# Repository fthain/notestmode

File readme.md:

## notestmode - PCB and PLD designs

(c) Finn Thain 2024-2025

This project is a test rig for a logic circuit which provides backward compatibility to 4 Mbit and 16 Mbit DRAM devices, so they can be used in systems like the [Macintosh II](https://en.wikipedia.org/wiki/Macintosh_II) which pre-date the relevant DRAM standards.

A detailed discussion of the compatibility issue can be found in [Apple Technical Note #176: Macintosh Memory Configurations](https://www.tech-insider.org/mac/research/acrobat/9204.pdf). In short, DRAM chips larger than 1 Mbit end up in test mode and the system fails its POST.

Over the years, engineers have found various solutions to this problem. The design published here takes the traditional approach that adds a programmable logic device (PLD or PAL) to each SIMM.

The PLD chip intercepts the /RAS, /CAS and /WE signals sent from the logic board and generates a gated, albeit delayed, /WE signal as well as /RAS and /CAS signals which are similarly delayed.

## Other solutions

- A SIMM design for 4 Mbit devices complete with schematics and gerbers is available at [https://github.com/garrettsworkshop/RAMSIMM-30](https://github.com/garrettsworkshop/RAMSIMM-30).
- Another SIMM design for 4 Mbit devices is available at [https://github.com/kr239/Macintosh-IIx-RAM-SIMM](https://github.com/kr239/Macintosh-IIx-RAM-SIMM) but this one relies on the timing characteristics of Micron MT4C1004 DRAMs.
- A PAL SIMM manufactured by Cubig was described in detail at [https://68kmla.org/bb/index.php?threads/please-help-me-figure-out-what-the-deal-is-with-this-iix-ram.35989/](https://68kmla.org/bb/index.php?threads/please-help-me-figure-out-what-the-deal-is-with-this-iix-ram.35989/).
- A design for a memory expansion board for the Apple IIgs using 4 Mbit devices is available at [https://gglabs.us/node/439](https://gglabs.us/node/439).

## SIMM modifications

The design published here is a "mod board" custom built for the SIMMs which I had on hand at the time. Each module comprises eight KM41C16000CK-6 chips having a 300 mil SOJ 26(24) footprint. Each chip has 16 Mbits, giving a total of 16 MB per module.

The CUPL logic is intended to be compatible with standard DRAM devices. The PLD implementation used an Atmel ATF16V8C-7JU which is readily available (as of 2025). A slightly faster part is also available, which might be useful, being that different DRAM devices will have slightly different timing requirements.

The [PCB design](https://oshpark.com/shared_projects/0zsSkGAM) could be modified using KiCAD to suit almost any existing SIMM that accomodates a parity chip. Being that the custom PCB piggy-backs onto the SIMM where the parity chip would go, the it has to conform to the parity chip's pinout and orientation.

The mod board taps into VCC and VSS, and drives /WE and /RAS, through the footprint where it is soldered onto the SIMM.  **The traces that meet the /RAS, /CAS, /CASP and /WE contacts at the SIMM edge connector must be severed at the connector. Those nets are to be driven by the PLD instead of the logic board.**

The edge connector contacts are then reconnected to PLD input pins by use of 3 jumper wires. Thus the PLD is interposed between the logic board and DRAM devices. A fourth jumper wire is needed to tie /CASP at the parity chip footprint to /CAS at a nearby DRAM chip.

When soldering to the edge connector, I used high temp (kapton) tape to prevent solder flowing to that area of the pad which makes contact with the socket. This is to prevent potential mechanical issues caused by variations in board thickness.

**A word to the wise: this kind of soldering requires specialized tools, materials and skills. Without those, accidental damage to the logic board is likely.**

## Memory tests

The system shown in the photo below is a Mac II with FDHD upgrade and 68030 accelerator card. It is shown in the 68 MB memory configuration which was successfully tested using [memtester](https://pyropus.ca./software/memtester/). Note that, in a 64 MB configuration, this system does not pass its POST, probably due to a ROM bug.

## Photos

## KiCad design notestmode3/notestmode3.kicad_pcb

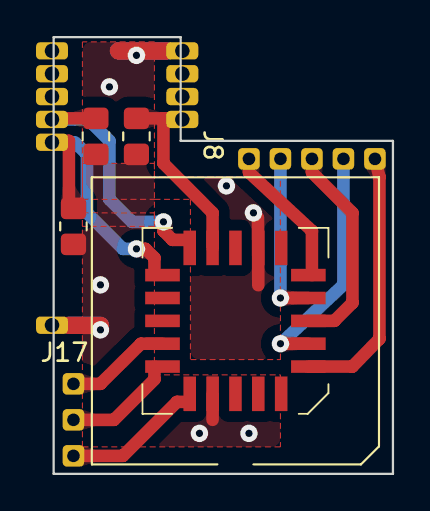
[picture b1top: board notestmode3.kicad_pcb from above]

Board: 2 copper layers, 18.8 x 24.3 mm, 14 parts (1 on the bottom side), 13 nets.

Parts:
C1: 220n; C_0805_2012Metric_Pad1.18x1.45mm_HandSolder
J1: SOJ 26(24); Castellations_2x13_P1.27mm_Vertical
J4, J5, J6, J7, J8, J17, J18, J19: SOLDER PAD; TestPoint_THTPad_D1.2mm_Drill0.7mm
R1, R2, R3: 2.2k; R_0805_2012Metric_Pad1.20x1.40mm_HandSolder
U2: GAL16V8; PLCC-20_SMD-Socket

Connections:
//CAS: J1.21, R3.2, U2.12 (IO8)
//MODULE_CAS: J6.1, U2.6 (I6)
//MODULE_RAS: J8.1, U2.8 (I8)
//MODULE_WE: J4.1, U2.4 (I4)
//RAS: J1.5, R1.2, U2.14 (IO6)
//WE: J1.4, R2.2, U2.13 (IO7)
unnamed: J5.1, U2.5 (I5)
unnamed: J7.1, U2.7 (I7)
unnamed: J17.1, U2.17 (I03)
unnamed: J18.1, U2.18 (IO2)
unnamed: J19.1, U2.19 (IO1)
VCC: C1.1, J1.12, R1.1, R2.1, R3.1, U2.20 (VCC)
VSS: C1.2, J1.24, U2.10 (GND)

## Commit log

2025-05-01 Some clarifications and additional information.
